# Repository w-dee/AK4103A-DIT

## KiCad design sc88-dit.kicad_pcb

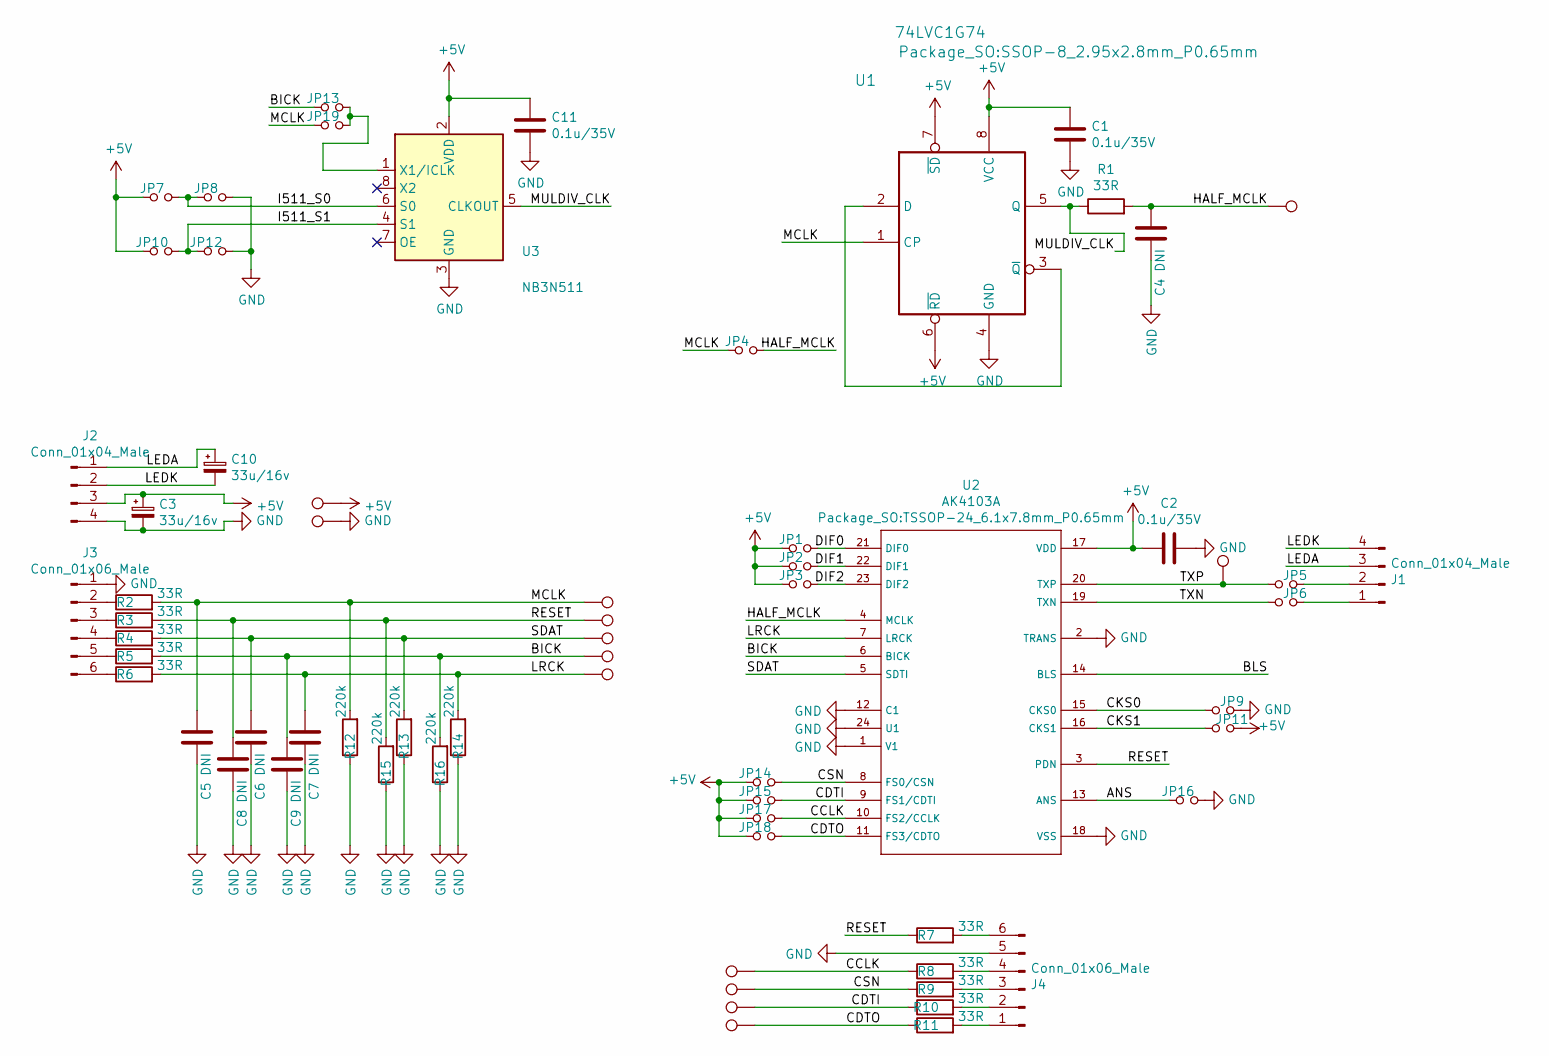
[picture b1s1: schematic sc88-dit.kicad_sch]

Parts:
C1, C2, C11: 0.1u/35V; C_0603_1608Metric_Pad1.05x0.95mm_HandSolder
C3, C10: 33u/16v; CP_Radial_D5.0mm_P2.50mm
C4, C5, C6, C7, C8, C9: DNI; C_0603_1608Metric_Pad1.05x0.95mm_HandSolder
J1, J2: Conn_01x04_Male; JST_XH_S4B-XH-A-1_1x04_P2.50mm_Horizontal
J3, J4: Conn_01x06_Male; JST_XH_S6B-XH-A-1_1x06_P2.50mm_Horizontal
JP1, JP2, JP3, JP4, JP5, JP6, JP7, JP8, JP9, JP10, JP11, JP12, JP13, JP14, JP15, JP16, JP17, JP18, JP19: Jumper_NO_Small; R_0603_1608Metric_SolderJumperCompatible
R1, R2, R3, R4, R5, R6, R7, R8, R9, R10, R11: 33R; R_0603_1608Metric_Pad1.05x0.95mm_HandSolder
R12, R13, R14, R15, R16: 220k; R_0603_1608Metric_Pad1.05x0.95mm_HandSolder
TP1, TP2, TP3, TP4, TP5, TP6, TP7, TP8, TP9, TP10, TP11, TP12, TP13: TestPoint; PinHeader_1x01_P2.54mm_Vertical
U1: 74LVC1G74; SSOP-8_2.95x2.8mm_P0.65mm
U2: AK4103A; TSSOP-24_6.1x7.8mm_P0.65mm
U3: NB3N511; SOIC-8_3.9x4.9mm_P1.27mm

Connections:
+5V: C1.1, C2.2, C3.1, C11.1, J2.3, JP1.1, JP2.1, JP3.1, JP7.1, JP10.1, JP11.1, JP14.1, JP15.1, JP17.1, JP18.1, TP2.1, U1.6 (~RD), U1.7 (~SD), U1.8 (VCC), U2.17 (VDD), U3.2 (VDD)
/ANS: JP16.1, U2.13 (ANS)
/BICK: C9.1, JP13.1, R5.2, R16.2, TP8.1, U2.6 (BICK)
/CCLK: JP17.2, R8.1, TP10.1, U2.10 (FS2/CCLK)
/CDTI: JP15.2, R10.1, TP12.1, U2.9 (FS1/CDTI)
/CDTO: JP18.2, R11.1, TP13.1, U2.11 (FS3/CDTO)
/CKS0: JP9.2, U2.15 (CKS0)
/CKS1: JP11.2, U2.16 (CKS1)
/CSN: JP14.2, R9.1, TP11.1, U2.8 (FS0/CSN)
/DIF0: JP1.2, U2.21 (DIF0)
/DIF1: JP2.2, U2.22 (DIF1)
/DIF2: JP3.2, U2.23 (DIF2)
/HALF_MCLK: C4.1, JP4.2, R1.2, TP1.1, U2.4 (MCLK)
/I511_S0: JP7.2, JP8.1, U3.6 (S0)
/I511_S1: JP10.2, JP12.1, U3.4 (S1)
/LEDA: C10.1, J1.3, J2.1
/LEDK: C10.2, J1.4, J2.2
/LRCK: C7.1, R6.2, R14.2, TP9.1, U2.7 (LRCK)
/MCLK: C5.1, JP4.1, JP19.1, R2.2, R12.2, TP5.1, U1.1 (CP)
/MULDIV_CLK: R1.1, U1.5 (Q), U3.5 (CLKOUT)
/RESET: C8.1, R3.2, R7.1, R15.2, TP6.1, U2.3 (PDN)
/SDAT: C6.1, R4.2, R13.2, TP7.1, U2.5 (SDTI)
/TXN: JP6.2, U2.19 (TXN)
/TXP: JP5.2, TP4.1, U2.20 (TXP)
GND: C1.2, C2.1, C3.2, C4.2, C5.2, C6.2, C7.2, C8.2, C9.2, C11.2, J2.4, J3.1, J4.5, JP8.2, JP9.1, JP12.2, JP16.2, R12.1, R13.1, R14.1, R15.1, R16.1, TP3.1, U1.4 (GND), U2.1 (V1), U2.2 (TRANS), U2.12 (C1), U2.18 (VSS), U2.24 (U1), U3.3 (GND)
unnamed: J1.1, JP6.1
unnamed: J1.2, JP5.1
unnamed: J3.2, R2.1
unnamed: J3.3, R3.1
unnamed: J3.4, R4.1
unnamed: J3.5, R5.1
unnamed: J3.6, R6.1
unnamed: J4.1, R11.2
unnamed: J4.2, R10.2
unnamed: J4.3, R9.2
unnamed: J4.4, R8.2
unnamed: J4.6, R7.2
unnamed: JP13.2, JP19.2, U3.1 (X1/ICLK)
unnamed: U1.2 (D), U1.3 (~Q)

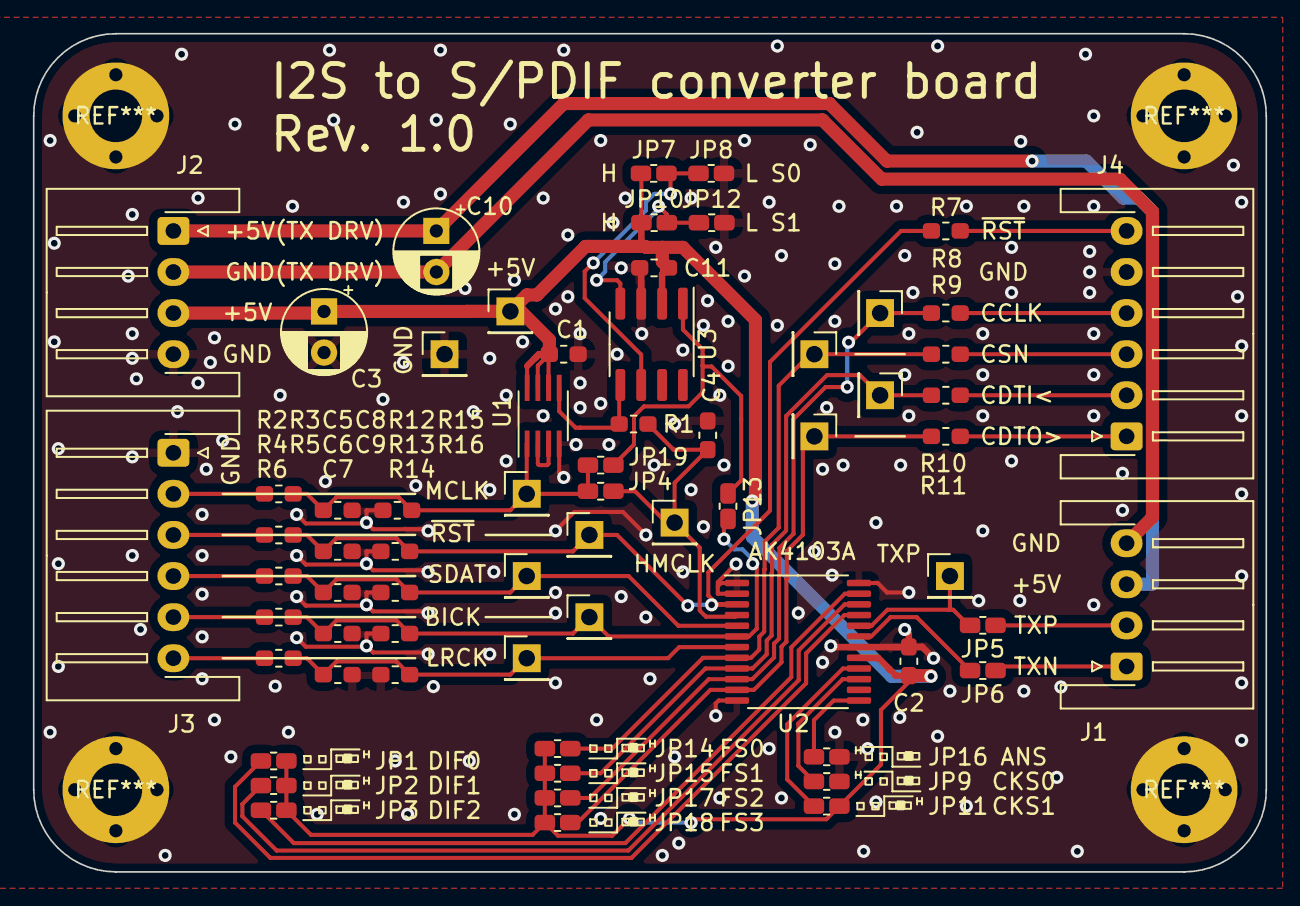
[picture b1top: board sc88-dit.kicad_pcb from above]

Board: 2 copper layers, 75.0 x 51.0 mm, 66 parts (0 on the bottom side), 39 nets.

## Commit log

2020-07-07 Added a readme
2020-07-07 Added TXP/TXN jumper(or resistor)
2020-07-07 Relocated freq. divider to make traces simple
2020-07-07 Silk refine
2020-07-07 Added an oppai-sauce logo
2020-07-08 To use right-angle connectors
2020-07-08 Refined VCC line
2020-07-10 Added NB3N511 clock multiplier to make MCLK from BCLK
2020-07-10 To be able to select multiplier's input from MCLK and BICK
2020-07-10 Added a description text on the board
2020-07-11 Added a schematic PDF
